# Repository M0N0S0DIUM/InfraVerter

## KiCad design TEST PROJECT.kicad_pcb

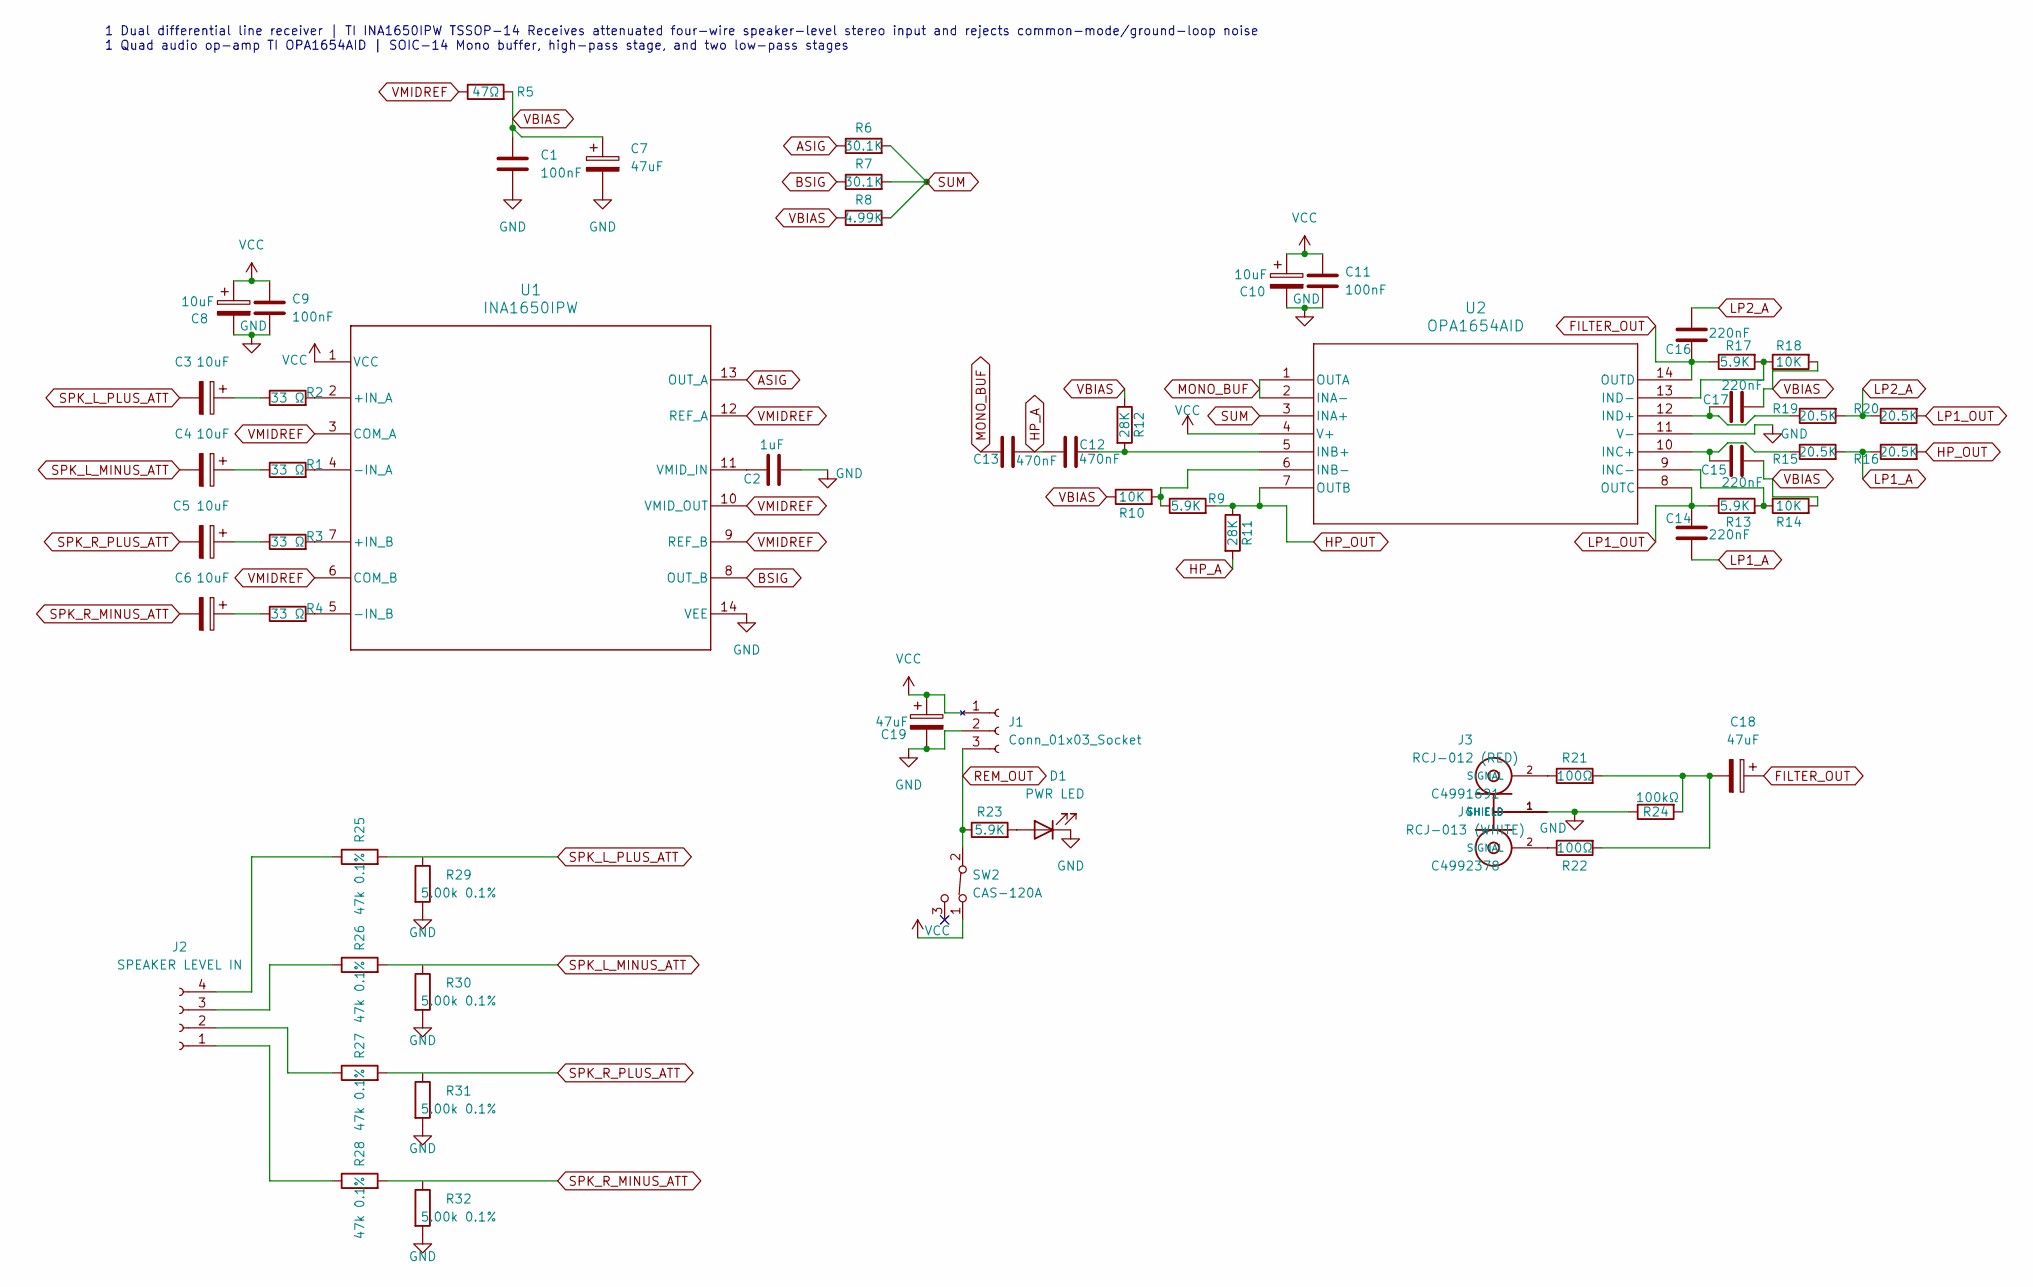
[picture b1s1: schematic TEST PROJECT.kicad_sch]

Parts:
C1, C9, C11: 100nF; C_0805_2012Metric_Pad1.18x1.45mm_HandSolder; JLC C286511
C2: 1uF; C_0805_2012Metric_Pad1.18x1.45mm_HandSolder; JLC C28323
C3, C4, C5, C6, C8, C10: 10uF; C_0805_2012Metric_Pad1.18x1.45mm_HandSolder; JLC C2164303
C7, C18, C19: 47uF; CP_Elec_6.3x5.4; JLC C30034
C12, C13: 470nF; C_0805_2012Metric_Pad1.18x1.45mm_HandSolder; JLC C13967
C14, C15, C16, C17: 220nF; C_0805_2012Metric_Pad1.18x1.45mm_HandSolder; JLC C129652
D1: PWR LED; LED_0805_2012Metric_Pad1.15x1.40mm_HandSolder; JLC C2297
J1: Conn_01x03_Socket; PhoenixContact_MSTBA_2,5_3-G-5,08_1x03_P5.08mm_Horizontal; JLC C8377
J2: SPEAKER LEVEL IN; PhoenixContact_MSTBA_2,5_4-G-5,08_1x04_P5.08mm_Horizontal; JLC C8446
J3: RCJ-012 (RED); RCA_CUI_RCJ-01X_RightAngle; MPN RCJ-012; JLC C4991691
J4: RCJ-013 (WHITE); RCA_CUI_RCJ-01X_RightAngle; MPN RCJ-013; JLC C4992378
R1, R2, R3, R4: 33 Ω; R_0805_2012Metric_Pad1.20x1.40mm_HandSolder; JLC C126353
R5: 47Ω; R_0805_2012Metric_Pad1.20x1.40mm_HandSolder; JLC C17714
R6, R7: 30.1K; R_0805_2012Metric_Pad1.20x1.40mm_HandSolder; JLC C163407
R8: 4.99K; R_0805_2012Metric_Pad1.20x1.40mm_HandSolder; JLC C114542
R9, R13, R17, R23: 5.9K; R_0805_2012Metric_Pad1.20x1.40mm_HandSolder; JLC C17730
R10, R14, R18: 10K; R_0805_2012Metric_Pad1.20x1.40mm_HandSolder; JLC C17414
R11, R12: 28K; R_0805_2012Metric_Pad1.20x1.40mm_HandSolder; JLC C17600
R15, R16, R19, R20: 20.5K; R_0805_2012Metric_Pad1.20x1.40mm_HandSolder; JLC C17537
R21, R22: 100Ω; R_0805_2012Metric_Pad1.20x1.40mm_HandSolder; JLC C844936
R24: 100kΩ; R_0805_2012Metric_Pad1.20x1.40mm_HandSolder; JLC C465471
R25, R26, R27, R28: 47k 0.1%; R_0805_2012Metric_Pad1.20x1.40mm_HandSolder; JLC C865515
R29, R30, R31, R32: 5.00k 0.1%; R_0805_2012Metric_Pad1.20x1.40mm_HandSolder; JLC C1698561
SW2: CAS-120A; Nidec_Copal_CAS-120A; JLC C5962834
U1: INA1650IPW; PW0014A_N; JLC C553130
U2: OPA1654AID; D14_TEX; JLC C30026

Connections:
ASIG: R6.1, U1.13 (OUT_A)
BSIG: R7.1, U1.8 (OUT_B)
FILTER_OUT: C16.1, C18.1, R17.1, U2.14 (OUTD)
GND: C1.2, C2.2, C7.2, C8.2, C9.2, C10.2, C11.2, C19.2, D1.1 (K), J1.2, J3.1 (SHIELD), J4.1 (SHIELD), R24.1, R29.2, R30.2, R31.2, R32.2, U1.14 (VEE), U2.11 (V-)
HP_A: C12.1, C13.2, R11.2
HP_OUT: R9.2, R11.1, R16.2, U2.7 (OUTB)
LP1_A: C14.2, R15.2, R16.1
LP1_OUT: C14.1, R13.1, R20.2, U2.8 (OUTC)
LP2_A: C16.2, R19.2, R20.1
MONO_BUF: C13.1, U2.1 (OUTA), U2.2 (INA-)
unnamed: C3.1, R2.1
unnamed: C4.1, R1.1
unnamed: C5.1, R3.1
unnamed: C6.1, R4.1
unnamed: C18.2, R21.2, R22.2, R24.2
unnamed: D1.2 (A), R23.2
unnamed: J2.1, R28.1
unnamed: J2.2, R27.1
unnamed: J2.3, R26.1
unnamed: J2.4, R25.1
unnamed: J3.2 (SIGNAL), R21.1
unnamed: J4.2 (SIGNAL), R22.1
unnamed: R2.2, U1.2 (+IN_A)
unnamed: R3.2, U1.7 (+IN_B)
unnamed: R1.2, U1.4 (-IN_A)
unnamed: R4.2, U1.5 (-IN_B)
unnamed: C2.1, U1.11 (VMID_IN)
unnamed: C12.2, R12.2, U2.5 (INB+)
unnamed: R9.1, R10.2, U2.6 (INB-)
unnamed: C15.1, R15.1, U2.10 (INC+)
unnamed: R13.2, R14.1, U2.9 (INC-)
unnamed: C17.1, R19.1, U2.12 (IND+)
unnamed: R17.2, R18.1, U2.13 (IND-)
REM_OUT: J1.3, R23.1, SW2.2 (COMMON)
SPK_L_MINUS_ATT: C4.2, R26.2, R30.1
SPK_L_PLUS_ATT: C3.2, R25.2, R29.1
SPK_R_MINUS_ATT: C6.2, R28.2, R32.1
SPK_R_PLUS_ATT: C5.2, R27.2, R31.1
SUM: R6.2, R7.2, R8.2, U2.3 (INA+)
VBIAS: C1.1, C7.1, C15.2, C17.2, R5.2, R8.1, R10.1, R12.1, R14.2, R18.2
VCC: C8.1, C9.1, C10.1, C11.1, C19.1, J1.1, SW2.1 (THROW_1), U1.1 (VCC), U2.4 (V+)
VMIDREF: R5.1, U1.3 (COM_A), U1.6 (COM_B), U1.9 (REF_B), U1.10 (VMID_OUT), U1.12 (REF_A)

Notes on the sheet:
1 Dual differential line receiver | TI INA1650IPW TSSOP-14 Receives attenuated four-wire speaker-level stereo input and rejects common-mode/ground-loop noise 1 Quad audio op-amp TI OPA1654AID | SOIC-14 Mono buffer, high-pass stage, and two low-pass stages

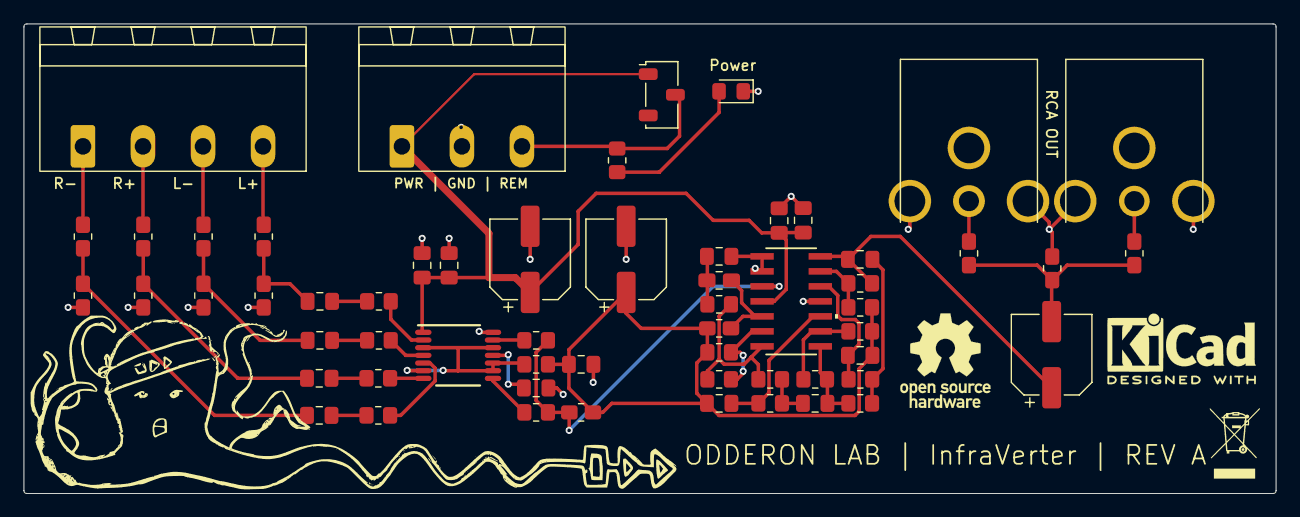
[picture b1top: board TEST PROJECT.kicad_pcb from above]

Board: 2 copper layers, 106.0 x 39.8 mm, 59 parts (0 on the bottom side), 42 nets.

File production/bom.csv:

Designator,Footprint,Quantity,Value,LCSC Part #
"C1, C11, C9",0805,3,100nF,C286511
"C10, C3, C4, C5, C6, C8",0805,6,10uF,C2164303
"C12, C13",0805,2,470nF,C13967
"C14, C15, C16, C17",0805,4,220nF,C129652
"C18, C19, C7",CP_Elec_6.3x5.4,3,47uF,C30034
C2,0805,1,1uF,C28323
D1,0805,1,PWR LED,C2297
J1,"PhoenixContact_MSTBA_2,5_3-G-5,08_1x03_P5.08mm_Horizontal",1,Conn_01x03_Socket,C8377
J2,"PhoenixContact_MSTBA_2,5_4-G-5,08_1x04_P5.08mm_Horizontal",1,SPEAKER LEVEL IN,C8446
J3,RCA_CUI_RCJ-01X_RightAngle,1,RCJ-012 (RED),C4992378
J4,RCA_CUI_RCJ-01X_RightAngle,1,RCJ-013 (WHITE),C4992378
"R1, R2, R3, R4",0805,4,33 Ω,C126353
"R10, R14, R18",0805,3,10K,C17414
"R11, R12",0805,2,28K,C17600
"R13, R17, R23, R9",0805,4,5.9K,C17730
"R15, R16, R19, R20",0805,4,20.5K,C17537
"R21, R22",0805,2,100Ω,C844936
R24,0805,1,100kΩ,C465471
"R25, R26, R27, R28",0805,4,47k 0.1%,C865515
"R29, R30, R31, R32",0805,4,5.00k 0.1%,C1698561
R5,0805,1,47Ω,C17714
"R6, R7",0805,2,30.1K,C163407
R8,0805,1,4.99K,C114542
SW2,Nidec_Copal_CAS-120A,1,CAS-120A,C5962834
U1,PW0014A_N,1,INA1650IPW,C553130
U2,D14_TEX,1,OPA1654AID,C30026
